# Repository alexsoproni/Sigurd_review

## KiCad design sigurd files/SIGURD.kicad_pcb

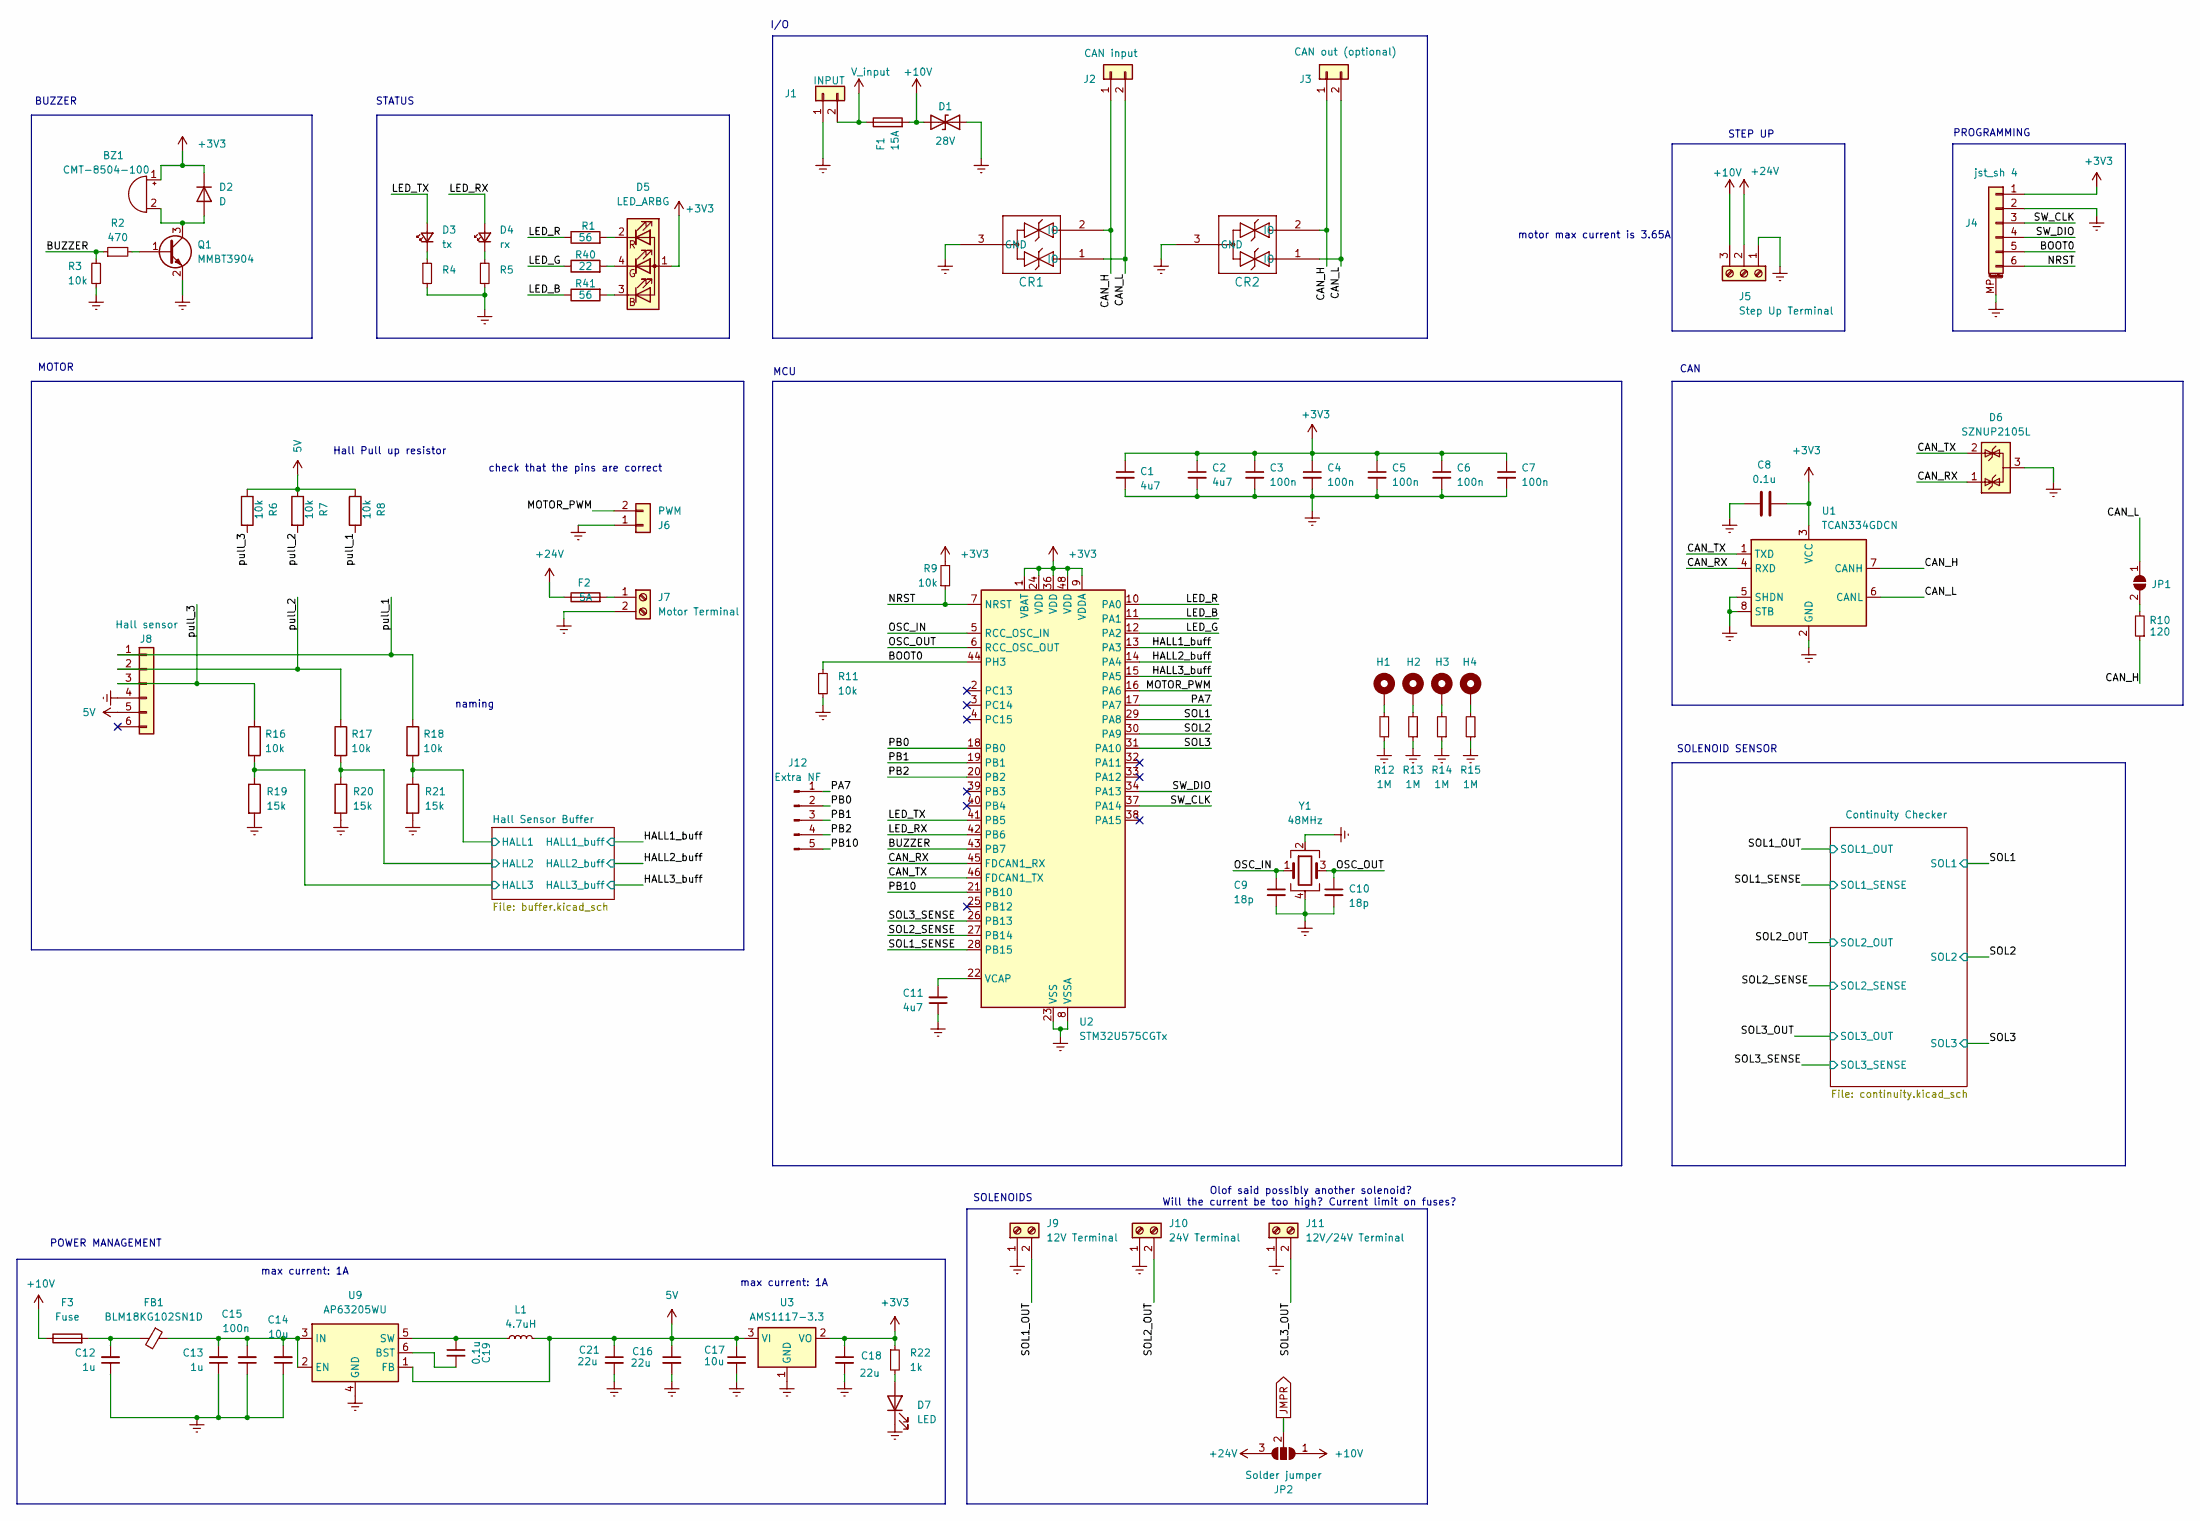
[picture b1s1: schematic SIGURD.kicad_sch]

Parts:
BZ1: CMT-8504-100; MagneticBuzzer_CUI_CMT-8504-100-SMT
C1, C2, C11: 4u7; C_0603_1608Metric_Pad1.08x0.95mm_HandSolder
C3, C4, C5, C6, C7, C15: 100n; C_0603_1608Metric_Pad1.08x0.95mm_HandSolder
C8, C19: 0.1u; C_0603_1608Metric_Pad1.08x0.95mm_HandSolder
C9, C10: 18p; C_0603_1608Metric_Pad1.08x0.95mm_HandSolder
C12, C13: 1u; C_0603_1608Metric_Pad1.08x0.95mm_HandSolder
C14, C17: 10u; C_0603_1608Metric_Pad1.08x0.95mm_HandSolder
C16, C18, C21: 22u; C_0603_1608Metric_Pad1.08x0.95mm_HandSolder
CR1, CR2: ESD2CAN36DBZRQ1; SOT-23-3_DBZ_TEX
D1: 28V; D_0603_1608Metric_Pad1.05x0.95mm_HandSolder
D2: D; D_SOD-523
D3: tx; LED_0603_1608Metric_Pad1.05x0.95mm_HandSolder
D4: rx; LED_0603_1608Metric_Pad1.05x0.95mm_HandSolder
D5: LED_ARBG; LED_Lumex_SML-LX0404SIUPGUSB
D6: SZNUP2105L; SOT-23
D7: LED; LED_0603_1608Metric_Pad1.05x0.95mm_HandSolder
F1: 15A; Fuse_1206_3216Metric
F2: 5A; Fuse_1206_3216Metric
F3: Fuse; Fuse_1206_3216Metric
FB1: BLM18KG102SN1D; L_0603_1608Metric_Pad1.05x0.95mm_HandSolder
H1, H2, H3, H4: MountingHole_Pad; MountingHole_3.2mm_M3_Pad_Via
J1: INPUT; JST_VH_B2P-VH-FB-B_1x02_P3.96mm_Vertical
J2: CAN input; JST_XH_B2B-XH-AM_1x02_P2.50mm_Vertical
J3: CAN out (optional); JST_XH_B2B-XH-AM_1x02_P2.50mm_Vertical
J4: jst_sh 4; JST_SH_SM06B-SRSS-TB_1x06-1MP_P1.00mm_Horizontal
J5: Step Up Terminal; TerminalBlock_Phoenix_MKDS-1,5-3_1x03_P5.00mm_Horizontal
J6: PWM; JST_XH_B2B-XH-A_1x02_P2.50mm_Vertical
J7: Motor Terminal; TerminalBlock_Phoenix_MKDS-1,5-2-5.08_1x02_P5.08mm_Horizont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
J8: Hall sensor; Molex_Micro-Fit_3.0_43045-0612_2x03_P3.00mm_Vertical
J9: 12V Terminal; TerminalBlock_Phoenix_MKDS-1,5-2-5.08_1x02_P5.08mm_Horizont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
J10: 24V Terminal; TerminalBlock_Phoenix_MKDS-1,5-2-5.08_1x02_P5.08mm_Horizont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
J11: 12V/24V Terminal; TerminalBlock_Phoenix_MKDS-1,5-2-5.08_1x02_P5.08mm_Horizont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
J12: Extra NF; PinHeader_1x05_P2.54mm_Vertical
JP1: SolderJumper_2_Open; SolderJumper-2_P1.3mm_Open_TrianglePad1.0x1.5mm
JP2: Solder jumper; SolderJumper-3_P2.0mm_Open_TrianglePad1.0x1.5mm
L1: 4.7uH; L_0603_1608Metric_Pad1.05x0.95mm_HandSolder
Q1: MMBT3904; SOT-23
R1: 56; LED_0603_1608Metric
R2: 470; R_0603_1608Metric_Pad0.98x0.95mm_HandSolder
R3, R6, R7, R8, R9, R11, R16, R17, R18: 10k; R_0603_1608Metric_Pad0.98x0.95mm_HandSolder
R4, R5: R_0603_1608Metric_Pad0.98x0.95mm_HandSolder
R10: 120; R_0603_1608Metric_Pad0.98x0.95mm_HandSolder
R12, R13, R14, R15: 1M; R_0603_1608Metric_Pad0.98x0.95mm_HandSolder
R19, R20, R21: 15k; R_0603_1608Metric_Pad0.98x0.95mm_HandSolder
R22: 1k; R_0603_1608Metric_Pad0.98x0.95mm_HandSolder
R40: 22; R_0603_1608Metric
R41: 56; R_0603_1608Metric
U1: TCAN334GDCN; TSOT-23-8
U2: STM32U575CGTx; LQFP-48_7x7mm_P0.5mm
U3: AMS1117-3.3; SOT-223-3_TabPin2
U9: AP63205WU; TSOT-23-6
Y1: 48MHz; Crystal_SMD_0603-4Pin_6.0x3.5mm_HandSoldering

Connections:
5V: C16.1, C17.1, C21.1, J8.5, L1.2, R6.1, R7.1, R8.1, U3.3 (VI), U9.1 (FB); also elsewhere on the board
+3V3: BZ1.1 (-), C1.1, C2.1, C3.1, C4.1, C5.1, C6.1, C7.1, C8.2, C18.1, D2.1 (K), D5.1 (A), J4.1, R9.2, R22.1, U1.3 (VCC), U2.1 (VBAT), U2.9 (VDDA), U2.24 (VDD), U2.36 (VDD), U2.48 (VDD), U3.2 (VO); also elsewhere on the board
+10V: D1.2 (A2), F1.2, F3.1, J5.3, JP2.1 (A); also elsewhere on the board
+24V: F2.1, J5.2, JP2.3 (B); also elsewhere on the board
/BOOT0: J4.5, R11.1, U2.44 (PH3); also elsewhere on the board
/BUZZER: R2.1, R3.2, U2.43 (PB7)
/CAN_H: CR1.2 (IO), CR2.2 (IO), J2.1, J3.1, R10.1, U1.7 (CANH); also elsewhere on the board
/CAN_L: CR1.1 (IO), CR2.1 (IO), J2.2, J3.2, JP1.1 (A), U1.6 (CANL); also elsewhere on the board
/CAN_RX: D6.1 (K), U1.4 (RXD), U2.45 (FDCAN1_RX)
/CAN_TX: D6.2 (K), U1.1 (TXD), U2.46 (FDCAN1_TX)
/HALL1_buff: U2.13 (PA3); also elsewhere on the board
/HALL2_buff: U2.14 (PA4); also elsewhere on the board
/HALL3_buff: U2.15 (PA5); also elsewhere on the board
/Hall Sensor Buffer/HALL1: R18.2, R21.1; also elsewhere on the board
/Hall Sensor Buffer/HALL2: R17.2, R20.1; also elsewhere on the board
/Hall Sensor Buffer/HALL3: R16.2, R19.1; also elsewhere on the board
/LED_B: R41.1, U2.11 (PA1)
/LED_G: R40.1, U2.12 (PA2)
/LED_R: R1.1, U2.10 (PA0)
/LED_RX: D4.2 (A), U2.42 (PB6)
/LED_TX: D3.2 (A), U2.41 (PB5)
/MOTOR_PWM: J6.2, U2.16 (PA6); also elsewhere on the board
/NRST: J4.6, R9.1, U2.7 (NRST); also elsewhere on the board
/OSC_IN: C9.1, U2.5 (RCC_OSC_IN), Y1.1
/OSC_OUT: C10.1, U2.6 (RCC_OSC_OUT), Y1.3
/PA7: J12.1, U2.17 (PA7)
/PB0: J12.2, U2.18 (PB0)
/PB1: J12.3, U2.19 (PB1)
/PB2: J12.4, U2.20 (PB2)
/PB10: J12.5, U2.21 (PB10)
/SOL1: U2.29 (PA8); also elsewhere on the board
/SOL1_OUT: J9.2; also elsewhere on the board
/SOL1_SENSE: U2.28 (PB15); also elsewhere on the board
/SOL2: U2.30 (PA9); also elsewhere on the board
/SOL2_OUT: J10.2; also elsewhere on the board
/SOL2_SENSE: U2.27 (PB14); also elsewhere on the board
/SOL3: U2.31 (PA10); also elsewhere on the board
/SOL3_OUT: J11.2; also elsewhere on the board
/SOL3_SENSE: U2.26 (PB13); also elsewhere on the board
/SW_CLK: J4.3, U2.37 (PA14); also elsewhere on the board
/SW_DIO: J4.4, U2.34 (PA13); also elsewhere on the board
/pull_1: J8.1, R8.2, R18.1; also elsewhere on the board
/pull_2: J8.2, R7.2, R17.1; also elsewhere on the board
/pull_3: J8.3, R6.2, R16.1; also elsewhere on the board
Earth: C1.2, C2.2, C3.2, C4.2, C5.2, C6.2, C7.2, C8.1, C9.2, C10.2, C11.1, C12.1, C13.1, C14.1, C15.1, C16.2, C17.2, C18.2, C21.2, CR1.3 (GND), CR2.3 (GND), D1.1 (A1), D6.3 (A), D7.1 (K), J1.1, J4.2, J4.MP (MountPin), J5.1, J6.1, J7.2, J8.4, J9.1, J10.1, J11.1, Q1.2 (E), R3.1, R4.2, R5.2, R11.2, R12.1, R13.1, R14.1, R15.1, R19.2, R20.2, R21.2, U1.2 (GND), U1.5 (SHDN), U1.8 (STB), U2.8 (VSSA), U2.23 (VSS), U2.35 (VSS), U2.47 (VSS), U3.1 (GND), U9.4 (GND), Y1.2, Y1.4; also elsewhere on the board
JMPR: JP2.2 (C); also elsewhere on the board
unnamed: BZ1.2 (+), D2.2 (A), Q1.3 (C)
unnamed: C12.2, F3.2, FB1.2
unnamed: D3.1 (K), R4.1
unnamed: D4.1 (K), R5.1
unnamed: D5.3 (BK), R41.2
unnamed: D5.4 (GK), R40.2
unnamed: D5.2 (RK), R1.2
unnamed: D7.2 (A), R22.2
unnamed: H1.1, R12.2
unnamed: H2.1, R13.2
unnamed: H3.1, R14.2
unnamed: H4.1, R15.2
unnamed 64: F2.2, J7.1; also elsewhere on the board
unnamed: JP1.2 (B), R10.2
unnamed: Q1.1 (B), R2.2
unnamed: C11.2, U2.22 (VCAP)
unnamed: C19.2, U9.6 (BST)
unnamed: C13.2, C14.2, C15.2, FB1.1, U9.2 (EN), U9.3 (IN)
unnamed: C19.1, L1.1, U9.5 (SW)
V_input: F1.1, J1.2; also elsewhere on the board

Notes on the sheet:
SOLENOIDS
BUZZER
I/O
Olof said possibly another solenoid?
Will the current be too high? Current limit on fuses?
check that the pins are correct
max current: 1A
STEP UP
SOLENOID SENSOR
PROGRAMMING
naming
CAN
POWER MANAGEMENT
motor max current is 3.65A
MOTOR
Hall Pull up resistor
MCU
STATUS

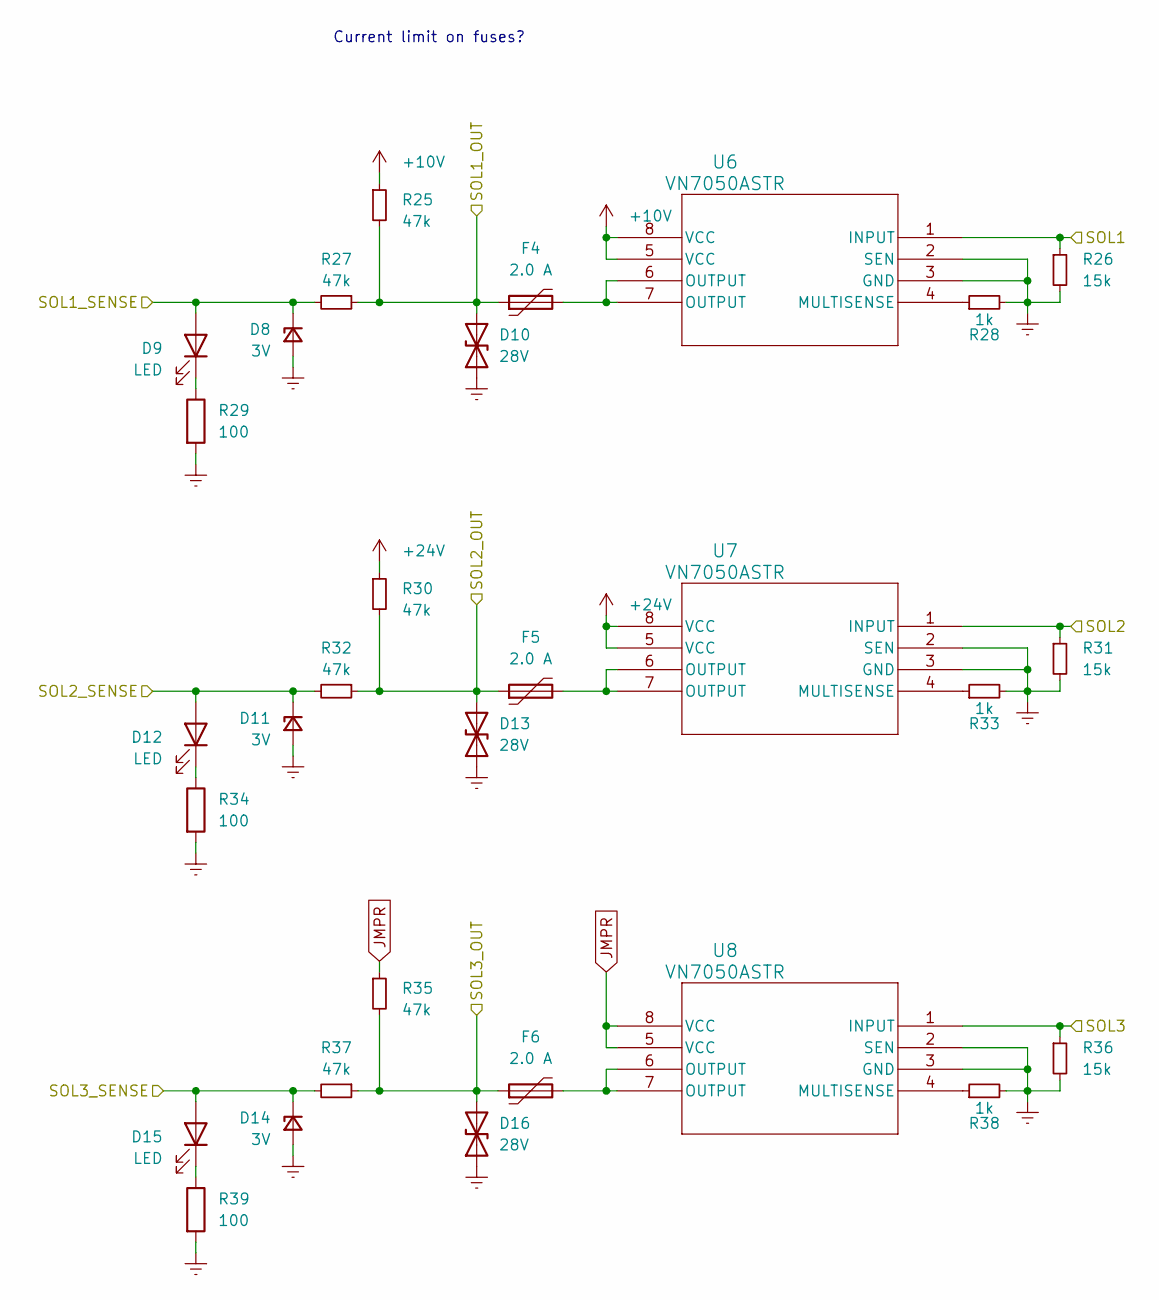
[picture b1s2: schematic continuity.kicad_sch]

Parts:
D8, D11, D14: 3V; D_SOD-323_HandSoldering
D9, D12, D15: LED; LED_0603_1608Metric_Pad1.05x0.95mm_HandSolder
D10, D13, D16: 28V; D_0603_1608Metric_Pad1.05x0.95mm_HandSolder
F4, F5, F6: 2.0 A; Fuse_1812_4532Metric
R25, R27, R30, R32, R35, R37: 47k; R_0603_1608Metric_Pad0.98x0.95mm_HandSolder
R26, R31, R36: 15k; R_0603_1608Metric_Pad0.98x0.95mm_HandSolder
R28, R33, R38: 1k; R_0603_1608Metric_Pad0.98x0.95mm_HandSolder
R29, R34, R39: 100; R_0603_1608Metric
U6, U7, U8: VN7050ASTR; SOIC_050ASTR_STM

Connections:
+10V: R25.1, U6.5 (VCC), U6.8 (VCC); also elsewhere on the board
+24V: R30.1, U7.5 (VCC), U7.8 (VCC); also elsewhere on the board
/SOL1: R26.1, U6.1 (INPUT); also elsewhere on the board
/SOL1_OUT: D10.2 (A2), F4.1, R25.2, R27.1; also elsewhere on the board
/SOL1_SENSE: D8.1 (K), D9.2 (A), R27.2; also elsewhere on the board
/SOL2: R31.1, U7.1 (INPUT); also elsewhere on the board
/SOL2_OUT: D13.2 (A2), F5.1, R30.2, R32.1; also elsewhere on the board
/SOL2_SENSE: D11.1 (K), D12.2 (A), R32.2; also elsewhere on the board
/SOL3: R36.1, U8.1 (INPUT); also elsewhere on the board
/SOL3_OUT: D16.2 (A2), F6.1, R35.2, R37.1; also elsewhere on the board
/SOL3_SENSE: D14.1 (K), D15.2 (A), R37.2; also elsewhere on the board
Earth: D8.2 (A), D10.1 (A1), D11.2 (A), D13.1 (A1), D14.2 (A), D16.1 (A1), R26.2, R28.2, R29.2, R31.2, R33.2, R34.2, R36.2, R38.2, R39.2, U6.2 (SEN), U6.3 (GND), U7.2 (SEN), U7.3 (GND), U8.2 (SEN), U8.3 (GND); also elsewhere on the board
JMPR: R35.1, U8.5 (VCC), U8.8 (VCC); also elsewhere on the board
unnamed: D9.1 (K), R29.1
unnamed: D12.1 (K), R34.1
unnamed: D15.1 (K), R39.1
unnamed: F4.2, U6.6 (OUTPUT), U6.7 (OUTPUT)
unnamed: F5.2, U7.6 (OUTPUT), U7.7 (OUTPUT)
unnamed: F6.2, U8.6 (OUTPUT), U8.7 (OUTPUT)
unnamed: R28.1, U6.4 (MULTISENSE)
unnamed: R33.1, U7.4 (MULTISENSE)
unnamed: R38.1, U8.4 (MULTISENSE)

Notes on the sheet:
Current limit on fuses?

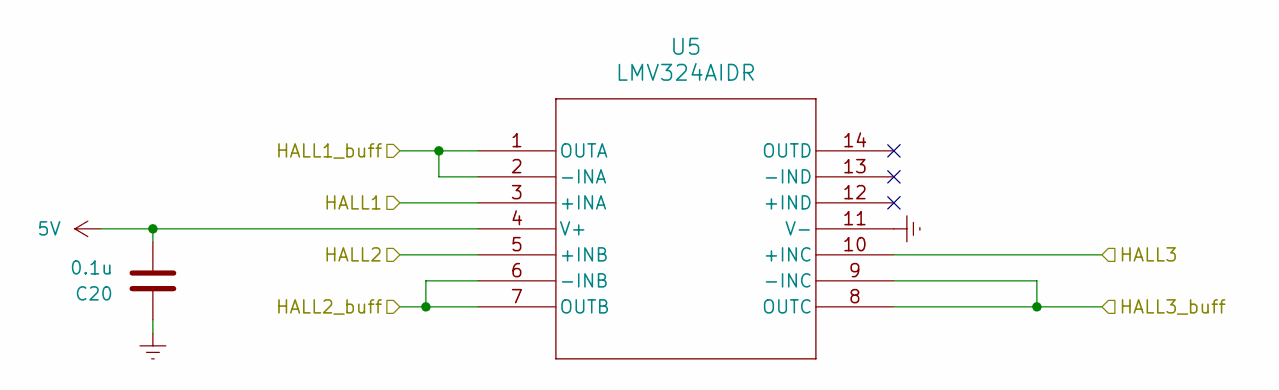
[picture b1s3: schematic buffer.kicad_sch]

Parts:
C20: 0.1u; C_0603_1608Metric_Pad1.08x0.95mm_HandSolder
U5: LMV324AIDR; D14_TEX

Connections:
5V: C20.2, U5.4 (V+); also elsewhere on the board
/HALL1_buff: U5.1 (OUTA), U5.2 (-INA); also elsewhere on the board
/HALL2_buff: U5.6 (-INB), U5.7 (OUTB); also elsewhere on the board
/HALL3_buff: U5.8 (OUTC), U5.9 (-INC); also elsewhere on the board
/Hall Sensor Buffer/HALL1: U5.3 (+INA); also elsewhere on the board
/Hall Sensor Buffer/HALL2: U5.5 (+INB); also elsewhere on the board
/Hall Sensor Buffer/HALL3: U5.10 (+INC); also elsewhere on the board
Earth: C20.1, U5.11 (V-); also elsewhere on the board

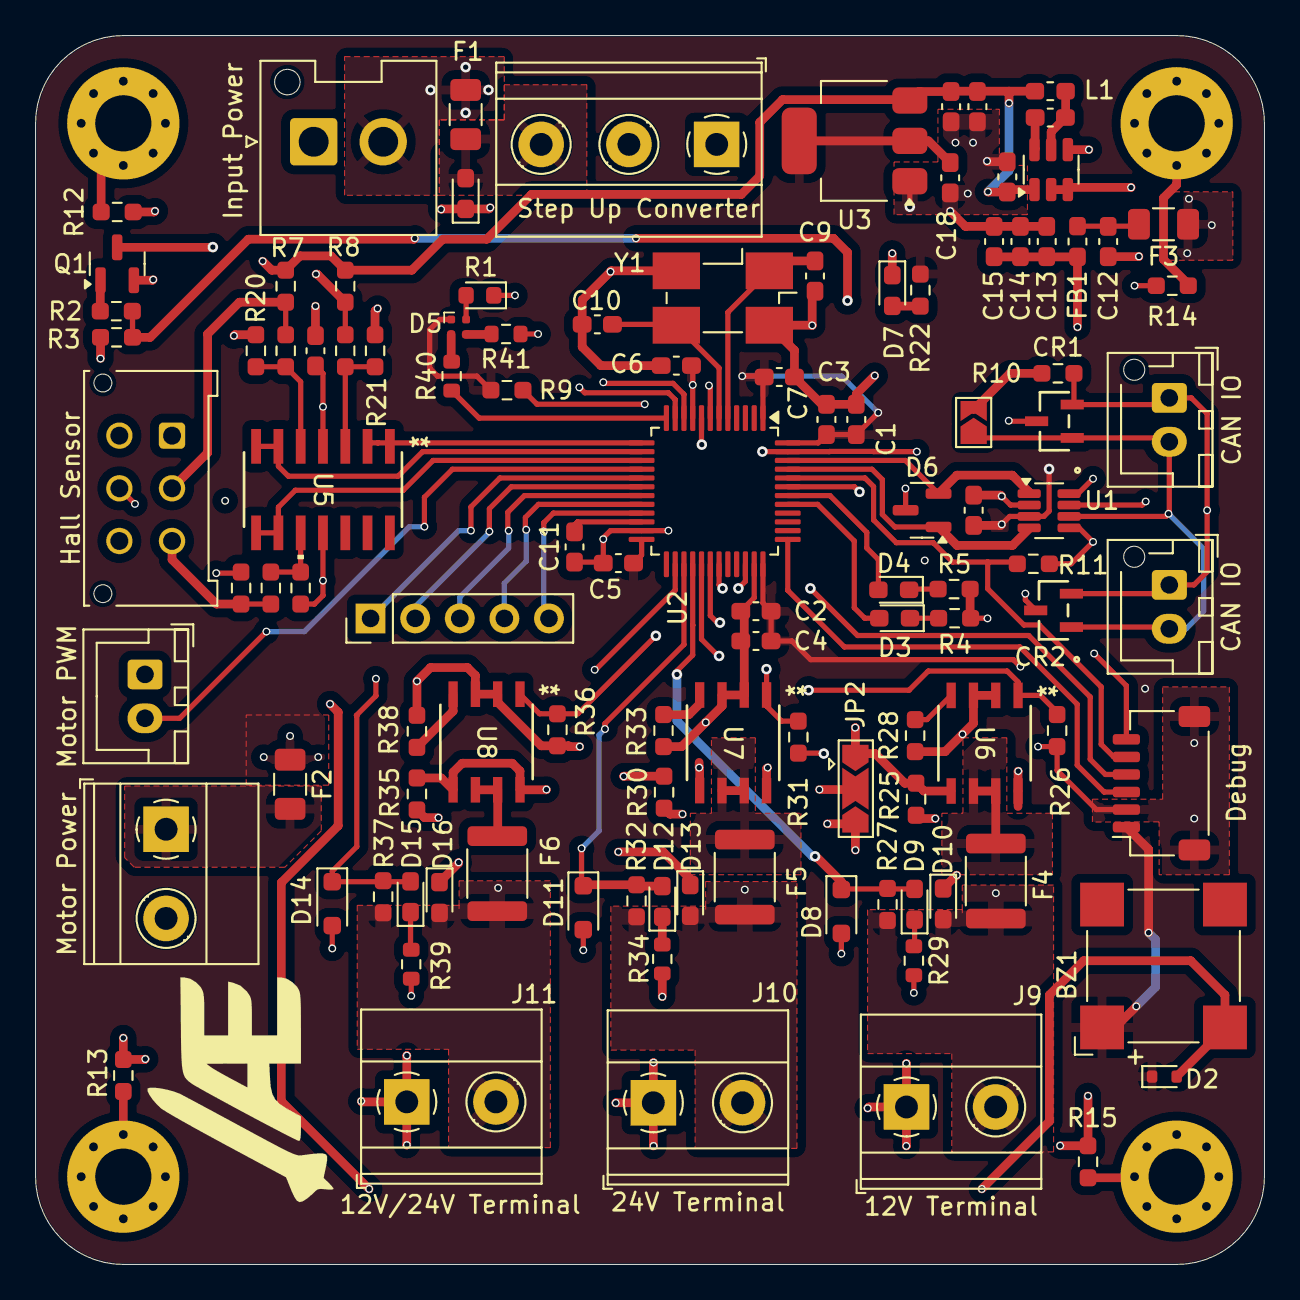
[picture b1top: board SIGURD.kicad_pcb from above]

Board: 4 copper layers, 70.0 x 70.0 mm, 115 parts (0 on the bottom side), 75 nets.

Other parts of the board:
CAN IO: CAN input; JST_XH_B2B-XH-AM_1x02_P2.50mm_Vertical
CAN IO#2: CAN out (optional); JST_XH_B2B-XH-AM_1x02_P2.50mm_Vertical
Debug: jst_sh 4; JST_SH_SM06B-SRSS-TB_1x06-1MP_P1.00mm_Horizontal
Hall Sensor: Hall sensor; Molex_Micro-Fit_3.0_43045-0612_2x03_P3.00mm_Vertical
Input Power: INPUT; JST_VH_B2P-VH-FB-B_1x02_P3.96mm_Vertical
Motor PWM: PWM; JST_XH_B2B-XH-A_1x02_P2.50mm_Vertical
Motor Power: Motor Terminal; TerminalBlock_Phoenix_MKDS-1,5-2-5.08_1x02_P5.08mm_Horizont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
Step Up Converter: Step Up Terminal; TerminalBlock_Phoenix_MKDS-1,5-3_1x03_P5.00mm_Horizontal

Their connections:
5V: Hall Sensor.5; also elsewhere on the board
+3V3: Debug.1; also elsewhere on the board
+10V: Step Up Converter.3; also elsewhere on the board
+24V: Step Up Converter.2; also elsewhere on the board
/BOOT0: Debug.5; also elsewhere on the board
/CAN_H: CAN IO.1, CAN IO#2.1; also elsewhere on the board
/CAN_L: CAN IO.2, CAN IO#2.2; also elsewhere on the board
/MOTOR_PWM: Motor PWM.2; also elsewhere on the board
/NRST: Debug.6; also elsewhere on the board
/SW_CLK: Debug.3; also elsewhere on the board
/SW_DIO: Debug.4; also elsewhere on the board
/pull_1: Hall Sensor.1; also elsewhere on the board
/pull_2: Hall Sensor.2; also elsewhere on the board
/pull_3: Hall Sensor.3; also elsewhere on the board
Earth: Debug.2, Debug.MP (MountPin), Hall Sensor.4, Input Power.1, Motor PWM.1, Motor Power.2, Step Up Converter.1; also elsewhere on the board
unnamed 64: Motor Power.1; also elsewhere on the board
V_input: Input Power.2; also elsewhere on the board

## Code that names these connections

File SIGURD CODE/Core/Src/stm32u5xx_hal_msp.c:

/* USER CODE BEGIN Header */
/**
  ******************************************************************************
  * @file         stm32u5xx_hal_msp.c
  * @brief        This file provides code for the MSP Initialization
  *               and de-Initialization codes.
  ******************************************************************************
  * @attention
  *
  * Copyright (c) 2025 STMicroelectronics.
  * All rights reserved.
  *
  * This software is licensed under terms that can be found in the LICENSE file
  * in the root directory of this software component.
  * If no LICENSE file comes with this software, it is provided AS-IS.
  *
  ******************************************************************************
  */
/* USER CODE END Header */

/* Includes ------------------------------------------------------------------*/
#include "main.h"
/* USER CODE BEGIN Includes */

/* USER CODE END Includes */

/* Private typedef -----------------------------------------------------------*/
/* USER CODE BEGIN TD */

/* USER CODE END TD */

/* Private define ------------------------------------------------------------*/
/* USER CODE BEGIN Define */

/* USER CODE END Define */

/* Private macro -------------------------------------------------------------*/
/* USER CODE BEGIN Macro */

/* USER CODE END Macro */

/* Private variables ---------------------------------------------------------*/
/* USER CODE BEGIN PV */

/* USER CODE END PV */

/* Private function prototypes -----------------------------------------------*/
/* USER CODE BEGIN PFP */

/* USER CODE END PFP */

/* External functions --------------------------------------------------------*/
/* USER CODE BEGIN ExternalFunctions */

/* USER CODE END ExternalFunctions */

/* USER CODE BEGIN 0 */

/* USER CODE END 0 */
/**
  * Initializes the Global MSP.
  */
void HAL_MspInit(void)
{

  /* USER CODE BEGIN MspInit 0 */

  /* USER CODE END MspInit 0 */

  __HAL_RCC_PWR_CLK_ENABLE();

  /* System interrupt init*/

  /* USER CODE BEGIN MspInit 1 */

  /* USER CODE END MspInit 1 */
}

/**
  * @brief FDCAN MSP Initialization
  * This function configures the hardware resources used in this example
  * @param hfdcan: FDCAN handle pointer
  * @retval None
  */
void HAL_FDCAN_MspInit(FDCAN_HandleTypeDef* hfdcan)
{
  GPIO_InitTypeDef GPIO_InitStruct = {0};
  RCC_PeriphCLKInitTypeDef PeriphClkInit = {0};
  if(hfdcan->Instance==FDCAN1)
  {
    /* USER CODE BEGIN FDCAN1_MspInit 0 */

    /* USER CODE END FDCAN1_MspInit 0 */

  /** Initializes the peripherals clock
  */
    PeriphClkInit.PeriphClockSelection = RCC_PERIPHCLK_FDCAN1;
    PeriphClkInit.Fdcan1ClockSelection = RCC_FDCAN1CLKSOURCE_PLL1;
    if (HAL_RCCEx_PeriphCLKConfig(&PeriphClkInit) != HAL_OK)
    {
      Error_Handler();
    }

    /* Peripheral clock enable */
    __HAL_RCC_FDCAN1_CLK_ENABLE();

    __HAL_RCC_GPIOB_CLK_ENABLE();
    /**FDCAN1 GPIO Configuration
    PB8     ------> FDCAN1_RX
    PB9     ------> FDCAN1_TX
    */
    GPIO_InitStruct.Pin = GPIO_PIN_8|GPIO_PIN_9;
    GPIO_InitStruct.Mode = GPIO_MODE_AF_PP;
    GPIO_InitStruct.Pull = GPIO_NOPULL;
    GPIO_InitStruct.Speed = GPIO_SPEED_FREQ_LOW;
    GPIO_InitStruct.Alternate = GPIO_AF9_FDCAN1;
    HAL_GPIO_Init(GPIOB, &GPIO_InitStruct);

    /* FDCAN1 interrupt Init */
    HAL_NVIC_SetPriority(FDCAN1_IT0_IRQn, 0, 0);
    HAL_NVIC_EnableIRQ(FDCAN1_IT0_IRQn);
    /* USER CODE BEGIN FDCAN1_MspInit 1 */

    /* USER CODE END FDCAN1_MspInit 1 */

  }

}

/**
  * @brief FDCAN MSP De-Initialization
  * This function freeze the hardware resources used in this example
  * @param hfdcan: FDCAN handle pointer
  * @retval None
  */
void HAL_FDCAN_MspDeInit(FDCAN_HandleTypeDef* hfdcan)
{
  if(hfdcan->Instance==FDCAN1)
  {
    /* USER CODE BEGIN FDCAN1_MspDeInit 0 */

    /* USER CODE END FDCAN1_MspDeInit 0 */
    /* Peripheral clock disable */
    __HAL_RCC_FDCAN1_CLK_DISABLE();

    /**FDCAN1 GPIO Configuration
    PB8     ------> FDCAN1_RX
    PB9     ------> FDCAN1_TX
    */
    HAL_GPIO_DeInit(GPIOB, GPIO_PIN_8|GPIO_PIN_9);

    /* FDCAN1 interrupt DeInit */
    HAL_NVIC_DisableIRQ(FDCAN1_IT0_IRQn);
    /* USER CODE BEGIN FDCAN1_MspDeInit 1 */

    /* USER CODE END FDCAN1_MspDeInit 1 */
  }

}

/**
  * @brief TIM_PWM MSP Initialization
  * This function configures the hardware resources used in this example
  * @param htim_pwm: TIM_PWM handle pointer
  * @retval None
  */
void HAL_TIM_PWM_MspInit(TIM_HandleTypeDef* htim_pwm)
{
  GPIO_InitTypeDef GPIO_InitStruct = {0};
  if(htim_pwm->Instance==TIM2)
  {
    /* USER CODE BEGIN TIM2_MspInit 0 */

    /* USER CODE END TIM2_MspInit 0 */
    /* Peripheral clock enable */
    __HAL_RCC_TIM2_CLK_ENABLE();

    __HAL_RCC_GPIOA_CLK_ENABLE();
    /**TIM2 GPIO Configuration
    PA0     ------> TIM2_CH1
    PA1     ------> TIM2_CH2
    PA2     ------> TIM2_CH3
    */
    GPIO_InitStruct.Pin = GPIO_PIN_0|GPIO_PIN_1|GPIO_PIN_2;
    GPIO_InitStruct.Mode = GPIO_MODE_AF_PP;
    GPIO_InitStruct.Pull = GPIO_NOPULL;
    GPIO_InitStruct.Speed = GPIO_SPEED_FREQ_LOW;
    GPIO_InitStruct.Alternate = GPIO_AF1_TIM2;
    HAL_GPIO_Init(GPIOA, &GPIO_InitStruct);

    /* USER CODE BEGIN TIM2_MspInit 1 */

    /* USER CODE END TIM2_MspInit 1 */
  }
  else if(htim_pwm->Instance==TIM3)
  {
    /* USER CODE BEGIN TIM3_MspInit 0 */

    /* USER CODE END TIM3_MspInit 0 */
    /* Peripheral clock enable */
    __HAL_RCC_TIM3_CLK_ENABLE();

    __HAL_RCC_GPIOA_CLK_ENABLE();
    /**TIM3 GPIO Configuration
    PA6     ------> TIM3_CH1
    */
    GPIO_InitStruct.Pin = GPIO_PIN_6;
    GPIO_InitStruct.Mode = GPIO_MODE_AF_PP;
    GPIO_InitStruct.Pull = GPIO_NOPULL;
    GPIO_InitStruct.Speed = GPIO_SPEED_FREQ_LOW;
    GPIO_InitStruct.Alternate = GPIO_AF2_TIM3;
    HAL_GPIO_Init(GPIOA, &GPIO_InitStruct);

    /* USER CODE BEGIN TIM3_MspInit 1 */

    /* USER CODE END TIM3_MspInit 1 */
  }

}

/**
  * @brief TIM_PWM MSP De-Initialization
  * This function freeze the hardware resources used in this example
  * @param htim_pwm: TIM_PWM handle pointer
  * @retval None
  */
void HAL_TIM_PWM_MspDeInit(TIM_HandleTypeDef* htim_pwm)
{
  if(htim_pwm->Instance==TIM2)
  {
    /* USER CODE BEGIN TIM2_MspDeInit 0 */

    /* USER CODE END TIM2_MspDeInit 0 */
    /* Peripheral clock disable */
    __HAL_RCC_TIM2_CLK_DISABLE();

    /**TIM2 GPIO Configuration
    PA0     ------> TIM2_CH1
    PA1     ------> TIM2_CH2
    PA2     ------> TIM2_CH3
    */
    HAL_GPIO_DeInit(GPIOA, GPIO_PIN_0|GPIO_PIN_1|GPIO_PIN_2);

    /* USER CODE BEGIN TIM2_MspDeInit 1 */

    /* USER CODE END TIM2_MspDeInit 1 */
  }
  else if(htim_pwm->Instance==TIM3)
  {
    /* USER CODE BEGIN TIM3_MspDeInit 0 */

    /* USER CODE END TIM3_MspDeInit 0 */
    /* Peripheral clock disable */
    __HAL_RCC_TIM3_CLK_DISABLE();

    /**TIM3 GPIO Configuration
    PA6     ------> TIM3_CH1
    */
    HAL_GPIO_DeInit(GPIOA, GPIO_PIN_6);

    /* USER CODE BEGIN TIM3_MspDeInit 1 */

    /* USER CODE END TIM3_MspDeInit 1 */
  }

}

/* USER CODE BEGIN 1 */

/* USER CODE END 1 */

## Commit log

2025-04-05 added relevant files
2025-04-21 funny fortnite
2025-04-21 big chungus wholesome 100
2025-04-21 Liugma
2025-04-21 Goober
2025-04-22 Everything but power traces routed
2025-04-27 BoogerAids
2025-04-27 Almost complete board
2025-05-08 fixed pcb errors and most warnings
2025-05-09 big chungus
2025-06-03 Added sigurd code
2025-06-22 Update main.c
    Fixed code
